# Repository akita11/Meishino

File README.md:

# Meishino (ver 1.2)

つくった基板を名刺代わりに。
裏面の空いているところ（以下の赤丸で示したエリア）に、自分の名前などをシルクで入れれば、オリジナル基板のできあがり。
あとは製造発注して、名刺代わりに配りましょう。
Arduino UNO互換機と使えます。

基板の製造と部品の調達・実装によって、以下の3パターンのいずれかを製作できます。
1. USB-シリアル変換モジュール使用(挿入実装のはんだ付けだけで作れます）
2. 基板のmicroUSBケーブルで使う(1個だけ表面実装部品(QFNパッケージ)のはんだ付けが必要です)
3. 基板の基板を直接USBコネクタに挿して使う(1個だけ表面実装部品(QFNパッケージ)のはんだ付けが必要です)

# 製造仕様

ガーバーデータ（Meishino_v12_gerber.zip）を使います。

挿入実装で使う場合(上記1.)は、板厚はいくつでもかまいませんが、名刺として使えるように薄くする(0.6mmなど)のがおすすめです。

表面実装ICを使う場合は、製造発注時には、板厚を以下のいずれかを選びます。
- 板厚を2.0mmとすると、USBコネクタへ直接挿して使うことができます。(上記の2.)
- 板厚を0.6mmとすると、microUSBケーブルを使うことができます。（以下のUSBコネクタ直挿しを使うためには、コネクタ部分に1.4mm程度の厚紙などをはさみます）（上記の2.または3.）
- 板厚を自由（標準は1.6mm）とする（上記の1.）

# 部品の調達と実装

以下のいずれかを選んで、部品表(Meishino_v12_bom.csv)の部品を[秋月電子](http://akizukidenshi.com/)から購入し、部品をはんだ付けします。
- 表面実装のIC(QFNパッケージ)をはんだ付けできる方：U3以外の部品を使用します
- 表面実装のIC(QFNパッケージ)をはんだ付けできない：U1,C4,C5,R8以外の部品を使用します

# Author

Junichi Akita (@akita11, akita@ifdl.jp)

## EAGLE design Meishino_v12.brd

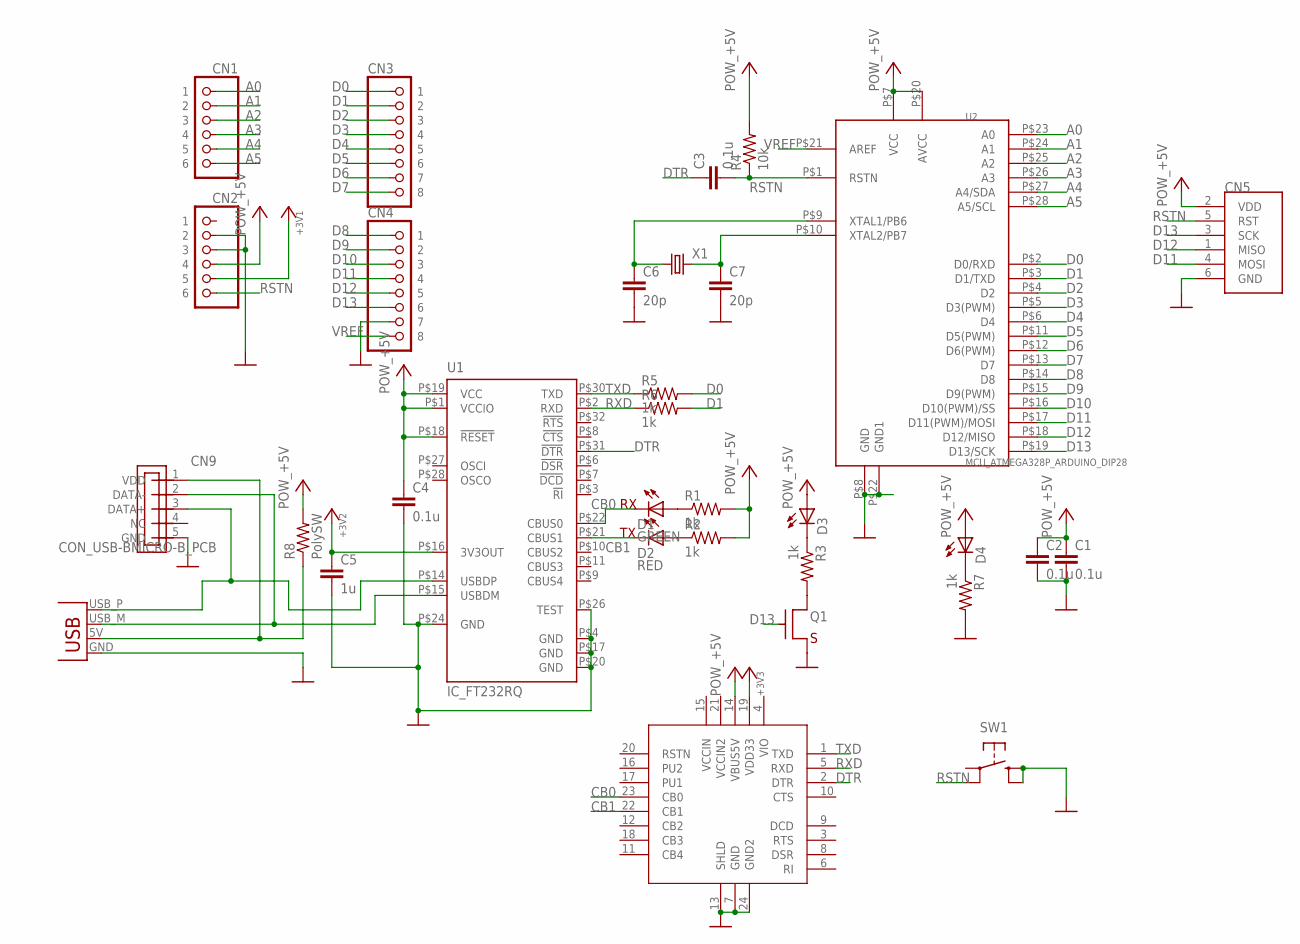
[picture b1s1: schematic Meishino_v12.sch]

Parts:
C1, C2, C3, C4: 0.1u; CAP_TH_5MM_L
C5: 1u; CAP_TH_5MM_L
C6, C7: 20p; CAP_TH_5MM_L
CN1, CN2: CON_PINHD-1X6; 1X06
CN3, CN4: CON_PINHD-1X8; 1X08
CN5: CON_AVRISPTH; 2X03R
CN9: CON_USB-BMICRO-B_PCB; USB-MICRO-PCB
D1: GREEN; SPARKFUN_LED5MM
D2: RED; SPARKFUN_LED5MM
D3, D4: LED5MM; SPARKFUN_LED5MM
JP2: CON_USBPCB; USB-A-PCB
Q1: TR_NMOS_2N7000; TO-92
R1, R2, R3, R5, R6, R7: 1k; R_TH_10MM_L
R4: 10k; R_TH_10MM_L
R8: PolySW; R_TH_10MM_L
SW1: SW_TACTTH; SW_B3F-10XX
U1: IC_FT232RQ; QFN32
U2: MCU_ATMEGA328P_ARDUINO_DIP28; DIP-28P(300MIL)
U3: MOD_AE_FT232_DIP24; DIP24_600MIL
X1: XTAL2HC49US; HC49US

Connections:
+3V3: C5.1, CN2.5, U1.P$16 (3V3OUT), U3.19 (VDD33)
+5V: C1.1, C2.1, C4.1, CN2.4, CN5.2 (VDD), D3.A, D4.A, R1.2, R2.2, R4.2, R8.2, U1.P$1 (VCCIO), U1.P$18 (!RESET), U1.P$19 (VCC), U2.P$7 (VCC), U2.P$20 (AVCC), U3.14 (VBUS5V)
A0: CN1.1, U2.P$23 (A0)
A1: CN1.2, U2.P$24 (A1)
A2: CN1.3, U2.P$25 (A2)
A3: CN1.4, U2.P$26 (A3)
A4: CN1.5, U2.P$27 (A4/SDA)
A5: CN1.6, U2.P$28 (A5/SCL)
CB0: D1.K (C), U1.P$22 (CBUS0), U3.23 (CB0)
CB1: D2.K (C), U1.P$21 (CBUS1), U3.22 (CB1)
D0: CN3.1, R5.2, U2.P$2 (D0/RXD)
D1: CN3.2, R6.2, U2.P$3 (D1/TXD)
D2: CN3.3, U2.P$4 (D2)
D3: CN3.4, U2.P$5 (D3(PWM))
D4: CN3.5, U2.P$6 (D4)
D5: CN3.6, U2.P$11 (D5(PWM))
D6: CN3.7, U2.P$12 (D6(PWM))
D7: CN3.8, U2.P$13 (D7)
D8: CN4.1, U2.P$14 (D8)
D9: CN4.2, U2.P$15 (D9(PWM))
D10: CN4.3, U2.P$16 (D10(PWM)/SS)
D11: CN4.4, CN5.4 (MOSI), U2.P$17 (D11(PWM)/MOSI)
D12: CN4.5, CN5.1 (MISO), U2.P$18 (D12/MISO)
D13: CN4.6, CN5.3 (SCK), Q1.2 (G), U2.P$19 (D13/SCK)
DTR: C3.1, U1.P$31 (!DTR), U3.2 (DTR)
GND: C1.2, C2.2, C4.2, C5.2, C6.2, C7.2, CN2.2, CN2.3, CN4.7, CN5.6 (GND), CN9.5 (GND), JP2.GND, Q1.1 (S), R7.2, SW1.1 (S), SW1.2 (S1), U1.P$4 (GND), U1.P$17 (GND), U1.P$20 (GND), U1.P$24 (GND), U1.P$26 (TEST), U2.P$8 (GND), U2.P$22 (GND1), U3.7 (GND), U3.13 (SHLD), U3.24 (GND2)
unnamed: D1.A, R1.1
unnamed: D2.A, R2.1
unnamed: D3.K (C), R3.1
unnamed: CN9.3 (DATA+), JP2.USB_P (D+), U1.P$14 (USBDP)
unnamed: CN9.2 (DATA-), JP2.USB_M (D-), U1.P$15 (USBDM)
unnamed: D4.K (C), R7.1
unnamed: C6.1, U2.P$9 (XTAL1/PB6), X1.1
unnamed: C7.1, U2.P$10 (XTAL2/PB7), X1.2
unnamed: CN9.1 (VDD), JP2.5V (VBUS), R8.1
unnamed: Q1.3 (D), R3.2
RSTN: C3.2, CN2.6, CN5.5 (RST), R4.1, SW1.4 (P1), U2.P$1 (RSTN)
RXD: R6.1, U1.P$2 (RXD), U3.5 (RXD)
TXD: R5.1, U1.P$30 (TXD), U3.1 (TXD)
VREF: CN4.8, U2.P$21 (AREF)

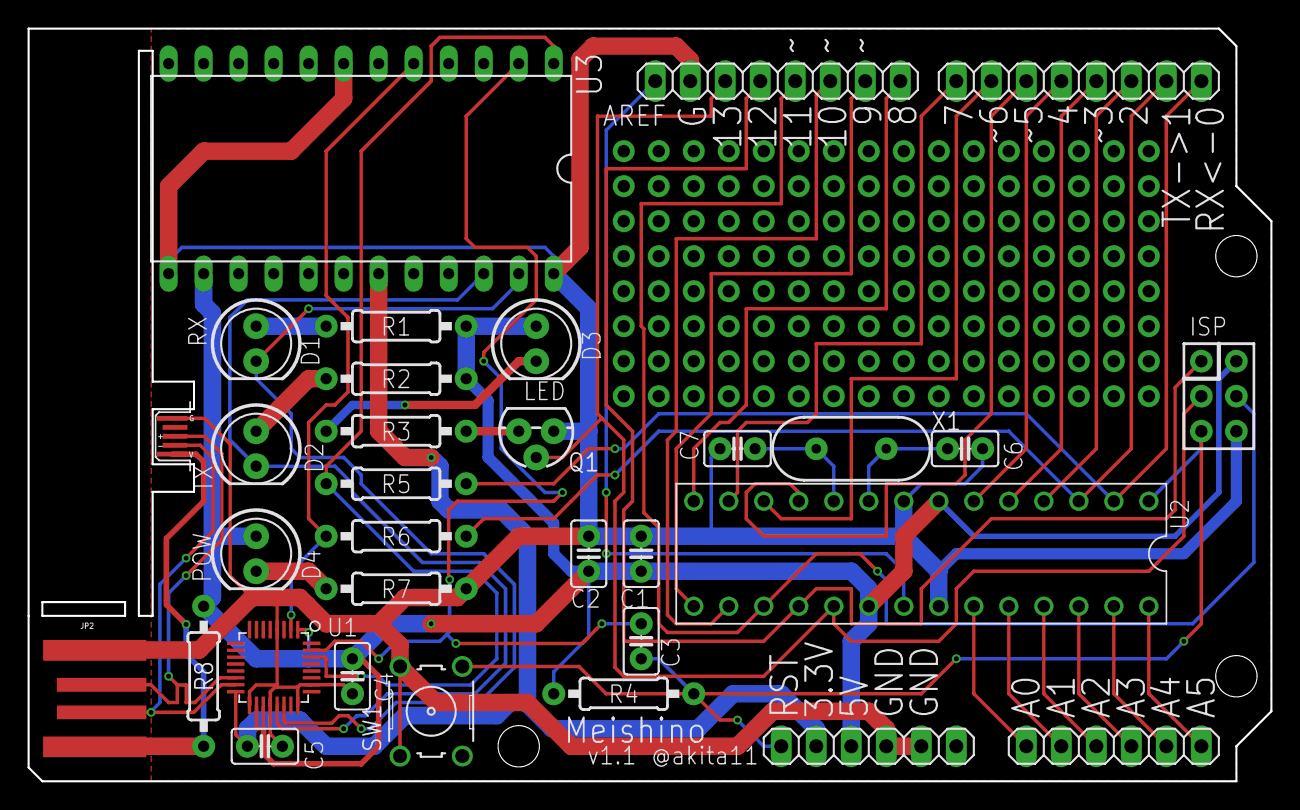
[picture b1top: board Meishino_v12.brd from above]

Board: 2 copper layers, 90.2 x 54.6 mm, 32 parts (0 on the bottom side), 40 nets.

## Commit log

2018-12-30 1st commit
2018-12-30 名前の記載エリア図を追加
2018-12-30 基板参照図の追加
2019-01-23 v1.1
2019-01-24 リセットとネジ穴を追加、シルクの調整。
2019-01-28 基板uUSBコネクタの形状を修正
2019-01-28 add license
2019-01-28 Create LICENSE
2019-02-21 ユニバーサルエリアのViaにStopがなかったのを修正(ver1.2)
